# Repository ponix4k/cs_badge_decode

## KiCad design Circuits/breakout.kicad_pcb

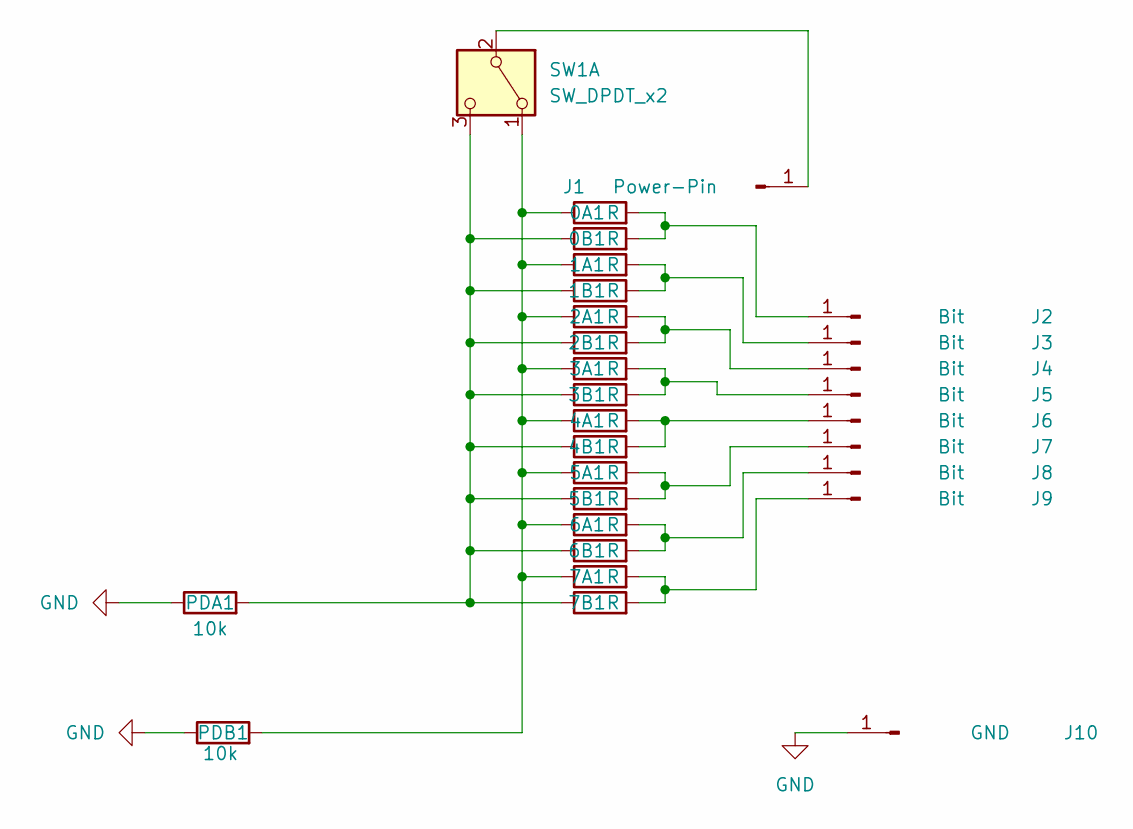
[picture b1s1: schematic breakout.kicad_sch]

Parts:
0A1, 0B1, 1A1, 1B1, 2A1, 2B1, 3A1, 3B1, 4A1, 4B1, 5A1, 5B1, 6A1, 6B1, 7A1, 7B1: R; R_1206_3216Metric
J1: Power-Pin; TestPoint_Pad_2.0x2.0mm
J2, J3, J4, J5, J6, J7, J8, J9: Bit; TestPoint_Pad_2.0x2.0mm
J10: GND; TestPoint_Pad_2.0x2.0mm
PDA1: 10k; R_1206_3216Metric
PDB1: 10k; R_1206_3216Metric
SW1: SW_DPDT_x2; SW_Slide_SPDT_Straight_CK_OS102011MS2Q

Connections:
GND: J10.1, PDA1.1, PDB1.1
unnamed: J1.1, SW1.2 (B)
unnamed: 0A1.2, 0B1.2, J2.1
unnamed: 1A1.2, 1B1.2, J3.1
unnamed: 2A1.2, 2B1.2, J4.1
unnamed: 3A1.2, 3B1.2, J5.1
unnamed: 4A1.2, 4B1.2, J6.1
unnamed: 5A1.2, 5B1.2, J7.1
unnamed: 6A1.2, 6B1.2, J8.1
unnamed: 7A1.2, 7B1.2, J9.1
unnamed: 0A1.1, 1A1.1, 2A1.1, 3A1.1, 4A1.1, 5A1.1, 6A1.1, 7A1.1, PDB1.2, SW1.1 (A)
unnamed: 0B1.1, 1B1.1, 2B1.1, 3B1.1, 4B1.1, 5B1.1, 6B1.1, 7B1.1, PDA1.2, SW1.3 (C)

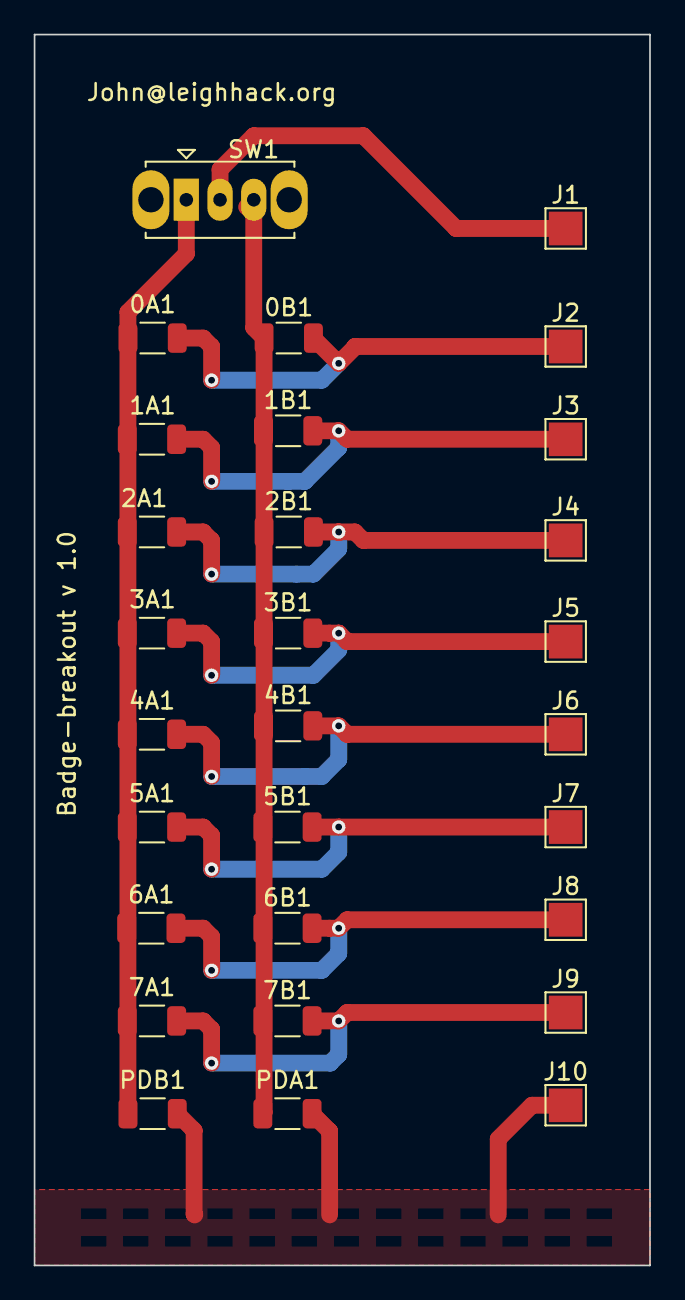
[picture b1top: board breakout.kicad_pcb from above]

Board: 2 copper layers, 36.5 x 73.0 mm, 29 parts (0 on the bottom side), 12 nets.

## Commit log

2024-04-10 inital commit
2024-04-20 Added code for relays to do the bit cycling
2024-06-10 Push final code
